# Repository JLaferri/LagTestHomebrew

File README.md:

Right now this readme will contain the very minimal information required to duplicate my lag tester. If anyone wants to make a more detailed guide I'm open to placing it here, or linking to it.

Here is a demonstation video of the device in use: https://www.youtube.com/watch?v=UTNUIQtreXQ

## Theory and Limitations
Currently this method only works using a Wii with homebrew channel installed. In order for the test to work you need to have a display that emits white light synced up with a sound cue. Both are picked up by the board and the offset is used to calculate the lag. The theory behind it is that the audio will never be delayed whereas the video will be. A CRT is used for calibration.

The Wii limitation could be eliminated if someone designed something else that created these same signals on generic displays. The nice thing about using the Wii is that you know you are providing the same output to the monitor that you would playing a smash game on Wii.

## Board
Click the following link to order some boards or download the gerbers:

<a href="https://oshpark.com/shared_projects/O6JRaha8"></img></a>

Another fab that I recommend if you want to get a few more made is https://www.seeedstudio.com/fusion_pcb.html

## Components
https://docs.google.com/spreadsheets/d/1Dj-m-Ip__IdE_k23mZq7f_099_O0pOspUQSO7Uzj5Qs/edit?usp=sharing

The above were the parts I used at some point... This was actually a long time ago so I'm not even sure how useful those part numbers are going to be but it's the best I have.

### Soldering Guide
This isn't really a guide so much as an aid to tell you where to place what components...
https://github.com/JLaferri/LagTestHomebrew/blob/master/SolderGuide.pdf

### Flashing the Processor
Once you have soldered the board together you will need to flash the processor with the code required to do the testing and run the display. The processor design is based on an Arduino and this can be done using the Arduino IDE. Open the IDE, select the correct programmer, and flash using the programmer. You will need a programmer such as https://www.sparkfun.com/products/9825

The Arduino file can be found here:
https://github.com/JLaferri/LagTestHomebrew/blob/master/Arduino%20Code/lagtester_current.ino

## Homebrew App
The following folder contains the app files to be used on homebrew channel on a hacked Wii
https://github.com/JLaferri/LagTestHomebrew/tree/master/HomebrewApp/compiled/LagTestHomebrew

### Building
For instructions on making changes to the app and building, go here: https://github.com/JLaferri/LagTestHomebrew/tree/master/HomebrewApp

## Additional Materials
Depending on what you intend to test you might need audio converters/extenders. Here are a few that I've used:
* https://www.amazon.com/gp/product/B00004Z5CP
* https://www.amazon.com/Female-Audio-Extension-Cable-CNE63133/dp/B00B973X20

You'll also need to purchase a 9V battery.

## Instructions
This sections explains how to actually use the tester

### Calibration
To add... I think it works kinda like the process in the next section but you gotta hold the button down first? I need to remember how to do this lol. Without calibrating, however, results will be meaningless. A "safe" CRT should be used to calibrate.

### Executing a Test
1. Ensure that the room you are testing in is not flooded with sunlight. The light sensor works by detecting lux and the sun will saturate the voltage output because it produces a lot of it. Too much artificial lighting is also not good but you should be fine as long as there's not a really bright light right behind the monitor you're testing or something.
2. Place a 9V battery in holder. The polarity is marked on the plastic. Do not reverse the polarity as I have not tested what would happen if you do. Worst case scenario, you'd fry the board. More likely though is that nothing would happen.
3. Plug audio cable into the device. Ideally this audio source comes directly from the Wii. In the case of the Sewell adapter use the cable I provided at its output and plug into board. If using component cables you might need to get an RCA connection extender for the audio to reach the device while maintaining mobility. You can also use the audio output of the monitor if it has one but you run the risk that if the monitor adds latency to the audio signal the measurement will be wrong.
4. Turn on the device by flipping the on off switch to on.
5. Boot into the homebrew app.
6. A white bar should be flashing on and off on the monitor, this is the test area. Place the device such that the clear light sensor on the bottom of the board is over the test area. For a CRT, keep a fair distance from the screen (probably at least 5 inches), you don't need to be overly precise about being directly in front of the test area on a CRT as it shoots out a fair amount of light. For an LCD I would recommend placing the sensor about half an inch to one inch away from the screen.
7. Holding the tester in place in front of the test area, press the push button on the top of the board. Wait until either an error code, indicated by the value Err#, or a result in milliseconds appears on the display.
8. Optionally take a few measurements to ensure repeatability.
9. Press A on the Wii Mote to move to the next test area.
10. Repeat steps 6 to 9 for the two other test areas (middle, bottom). Taking an equal amount of measurements for each.
11. Average all results to get the average frame lag of the display. On a CRT this should be close to 8.33 ms.

### Error codes
* Err0 - Audio is not begin detected. Either the amplitude of the audio signal has been reduced (via turning down the volume of a monitor output for example), the homebrew application is not running, or the cable is not plugged in.
* Err1 - Audio cable was disconnected during test?
* Err2 - Audio signal is stuck high for some reason. Not sure what would cause this.
* Err3 - Video signal difference between black and white is not large enough. Is the sensor in front of the test area?

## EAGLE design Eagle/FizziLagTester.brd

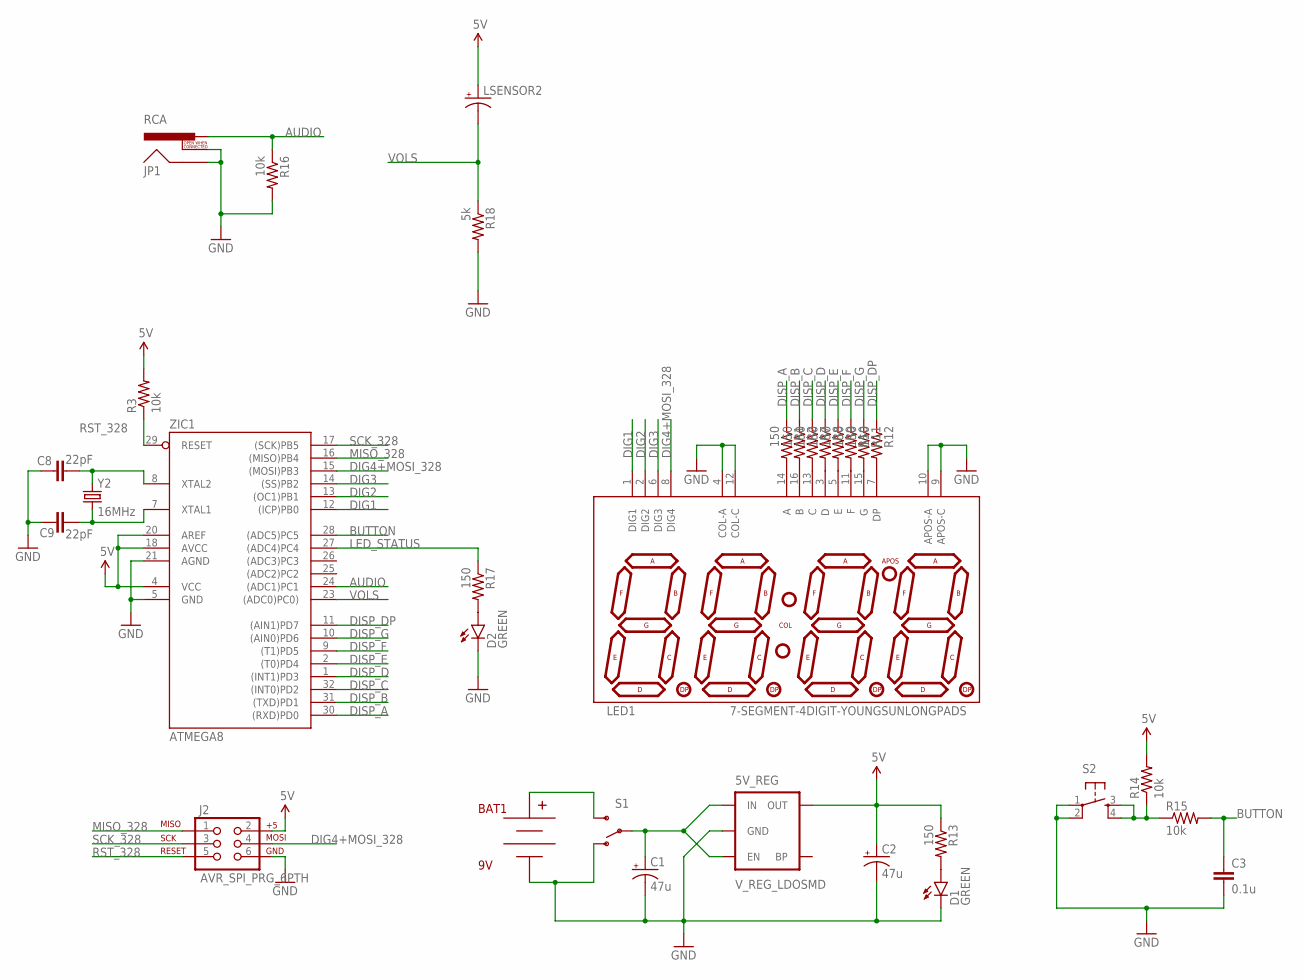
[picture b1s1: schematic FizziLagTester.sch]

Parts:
5V_REG: V_REG_LDOSMD; SOT23-5
BAT1: 9V; BC9VPC
C1, C2: 47u; CPOL-RADIAL-100UF-25V
C3: 0.1u; 0603-CAP
C8, C9: 22pF; 0603-CAP
D1, D2: GREEN; LED-0603
J2: AVR_SPI_PRG_6PTH; 2X3
JP1: RCA
LED1: 7-SEGMENT-4DIGIT-YOUNGSUNLONGPADS; 7-SEGMENT-4DIGIT-YOUNGSUN-LONGPADS
LSENSOR2: CAP_POLPTH2; CPOL-RADIAL-10UF-25V
R1, R2, R7, R8, R9, R10, R11, R12, R13, R17: 150; 0603-RES
R3, R14, R15, R16: 10k; 0603-RES
R18: 5k; 0603-RES
S1: SWITCH-SPDTPTH; SWITCH-SPDT
S2: TAC_SWITCHPTH; TACTILE-PTH
Y2: 16MHz; HC49US
ZIC1: ATMEGA8; TQFP32-08

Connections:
5V: 5V_REG.5 (OUT), C2.1 (+), J2.2, LSENSOR2.1 (+), R3.2, R13.1, R14.2, ZIC1.4 (VCC), ZIC1.18 (AVCC), ZIC1.20 (AREF)
AUDIO: JP1.PIN, R16.1, ZIC1.24 ((ADC1)PC1)
BUTTON: C3.1, R15.2, ZIC1.28 ((ADC5)PC5)
DIG1: LED1.1 (DIG1), ZIC1.12 ((ICP)PB0)
DIG2: LED1.2 (DIG2), ZIC1.13 ((OC1)PB1)
DIG3: LED1.6 (DIG3), ZIC1.14 ((SS)PB2)
DIG4+MOSI_328: J2.4, LED1.8 (DIG4), ZIC1.15 ((MOSI)PB3)
DISP_A: R1.1, ZIC1.30 ((RXD)PD0)
DISP_B: R2.1, ZIC1.31 ((TXD)PD1)
DISP_C: R7.1, ZIC1.32 ((INT0)PD2)
DISP_D: R8.1, ZIC1.1 ((INT1)PD3)
DISP_DP: R12.1, ZIC1.11 ((AIN1)PD7)
DISP_E: R9.1, ZIC1.2 ((T0)PD4)
DISP_F: R10.1, ZIC1.9 ((T1)PD5)
DISP_G: R11.1, ZIC1.10 ((AIN0)PD6)
GND: 5V_REG.2 (GND), BAT1.V-, C1.2 (-), C2.2 (-), C3.2, C8.2, C9.2, D1.C, D2.C, J2.6, JP1.SHELL, JP1.SWITCH, LED1.4 (COL-A), LED1.9 (APOS-C), LED1.10 (APOS-A), LED1.12 (COL-C), R16.2, R18.2, S1.1 (O), S2.1, S2.2, ZIC1.5 (GND), ZIC1.21 (AGND)
LED_STATUS: R17.1, ZIC1.27 ((ADC4)PC4)
MISO_328: J2.1, ZIC1.16 ((MISO)PB4)
unnamed: LED1.14 (A), R1.2
unnamed: LED1.16 (B), R2.2
unnamed: C8.1, Y2.2, ZIC1.8 (XTAL2)
unnamed: C9.1, Y2.1, ZIC1.7 (XTAL1)
unnamed: LED1.13 (C), R7.2
unnamed: LED1.3 (D), R8.2
unnamed: LED1.5 (E), R9.2
unnamed: LED1.11 (F), R10.2
unnamed: LED1.15 (G), R11.2
unnamed: LED1.7 (DP), R12.2
unnamed: BAT1.V+, S1.3 (S)
unnamed: 5V_REG.1 (IN), 5V_REG.3 (EN), C1.1 (+), S1.2
unnamed: D1.A, R13.2
unnamed: R14.1, R15.1, S2.3, S2.4
unnamed: D2.A, R17.2
RST_328: J2.5, R3.1, ZIC1.29 (RESET)
SCK_328: J2.3, ZIC1.17 ((SCK)PB5)
VOLS: LSENSOR2.2 (-), R18.1, ZIC1.23 ((ADC0)PC0))

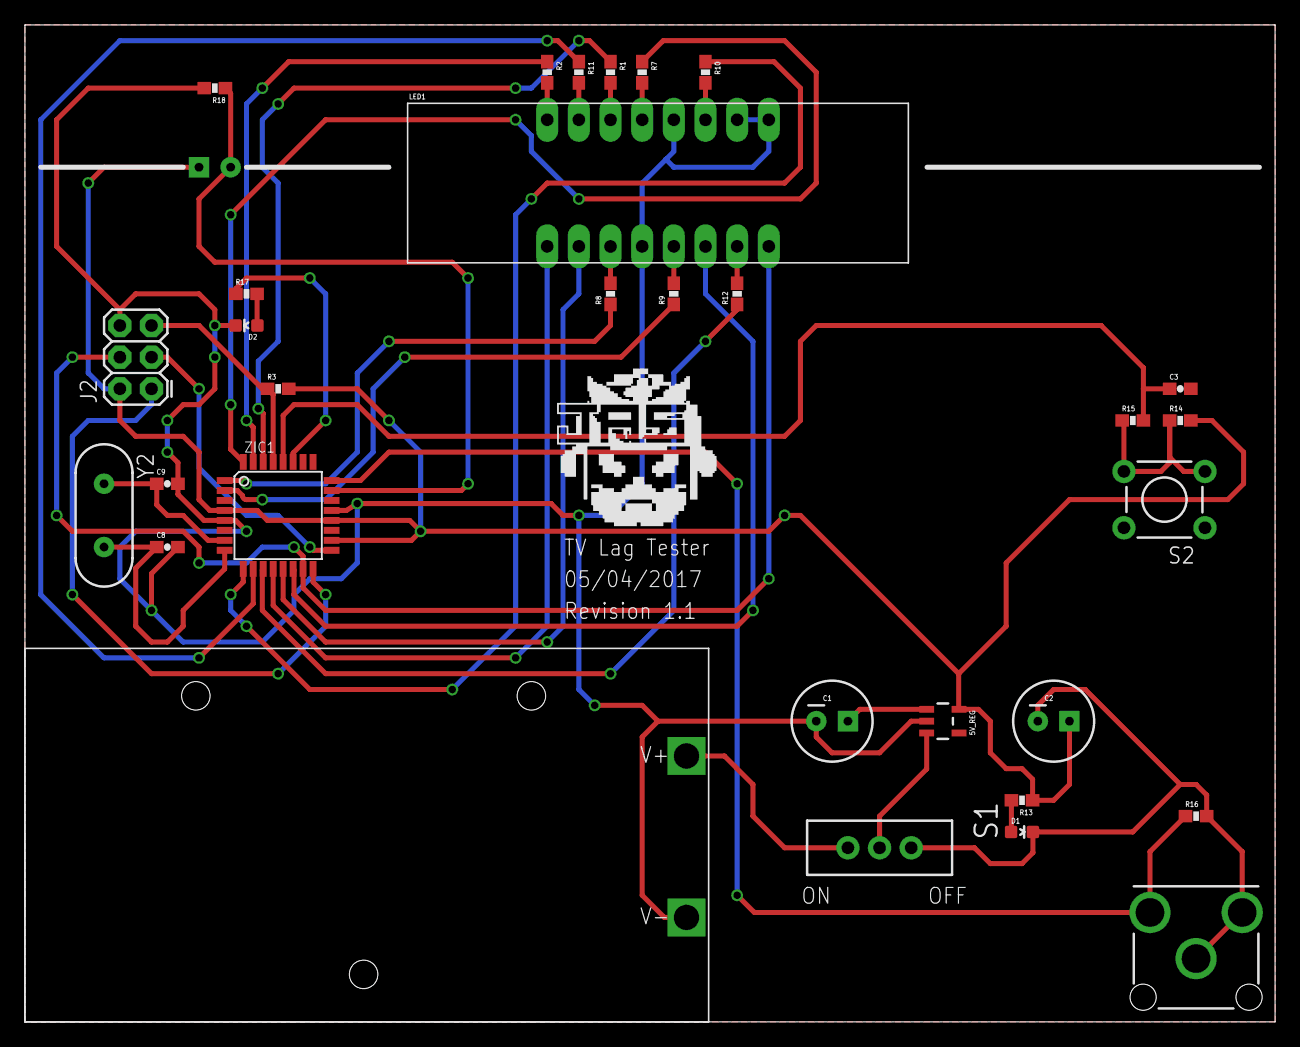
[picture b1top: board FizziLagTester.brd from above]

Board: 2 copper layers, 100.3 x 80.0 mm, 32 parts (1 on the bottom side), 36 nets.

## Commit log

2014-11-12 :confetti_ball: Added .gitattributes
2014-11-12 remove compiled files
2014-11-12 added ignored files to ignore
2016-01-13 Added some files
2017-01-24 Reorganization
    Adds some files and reorganizes stuff
2017-01-24 Adds homebrew compiled
2017-05-05 Adds in-progress eagle file
2017-05-05 Ignores eagle temp files
2017-05-06 I think revision 1.1 should be functional...
2018-04-10 add extra dependencies
2018-04-10 reorganize, add readme for homebrew app

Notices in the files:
parts and their libraries:
SparkFun-PowerIC: Licensing: CC v3.0 Share-Alike You are welcome to use this library for commercial purposes.
SparkFun-LED: Licensing: Creative Commons ShareAlike 4.0 International - https://creativecommons.org/licenses/by-sa/4.0
